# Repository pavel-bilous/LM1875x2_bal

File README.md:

# Two paralleled LM1875 ICs schematics and PCB design

Benefits of using two chips in parallel include: increase of the output drive capability of an amplifier, reduced voltage noise (better SNR), and reduced output offset error.

Resources used to design this amp:

Official datasheet - [https://www.ti.com/lit/gpn/lm1875](https://www.ti.com/lit/gpn/lm1875)

## PCB rendered in 3d:

## Schematics:

Two paralleled LM1875 are used to double the current drive and to increase the power output. Safe voltage to power the amplifier is 28V.
Gain is set to a minimum recommended in the datasheet of 10 V/V.

## PCB layout:

Bottom layer is GND. Top layer is signal + power and GND poured in between. Stiching vias are then applied to connect bottom and top GND planes to ensure those are as close to 0 as possible.

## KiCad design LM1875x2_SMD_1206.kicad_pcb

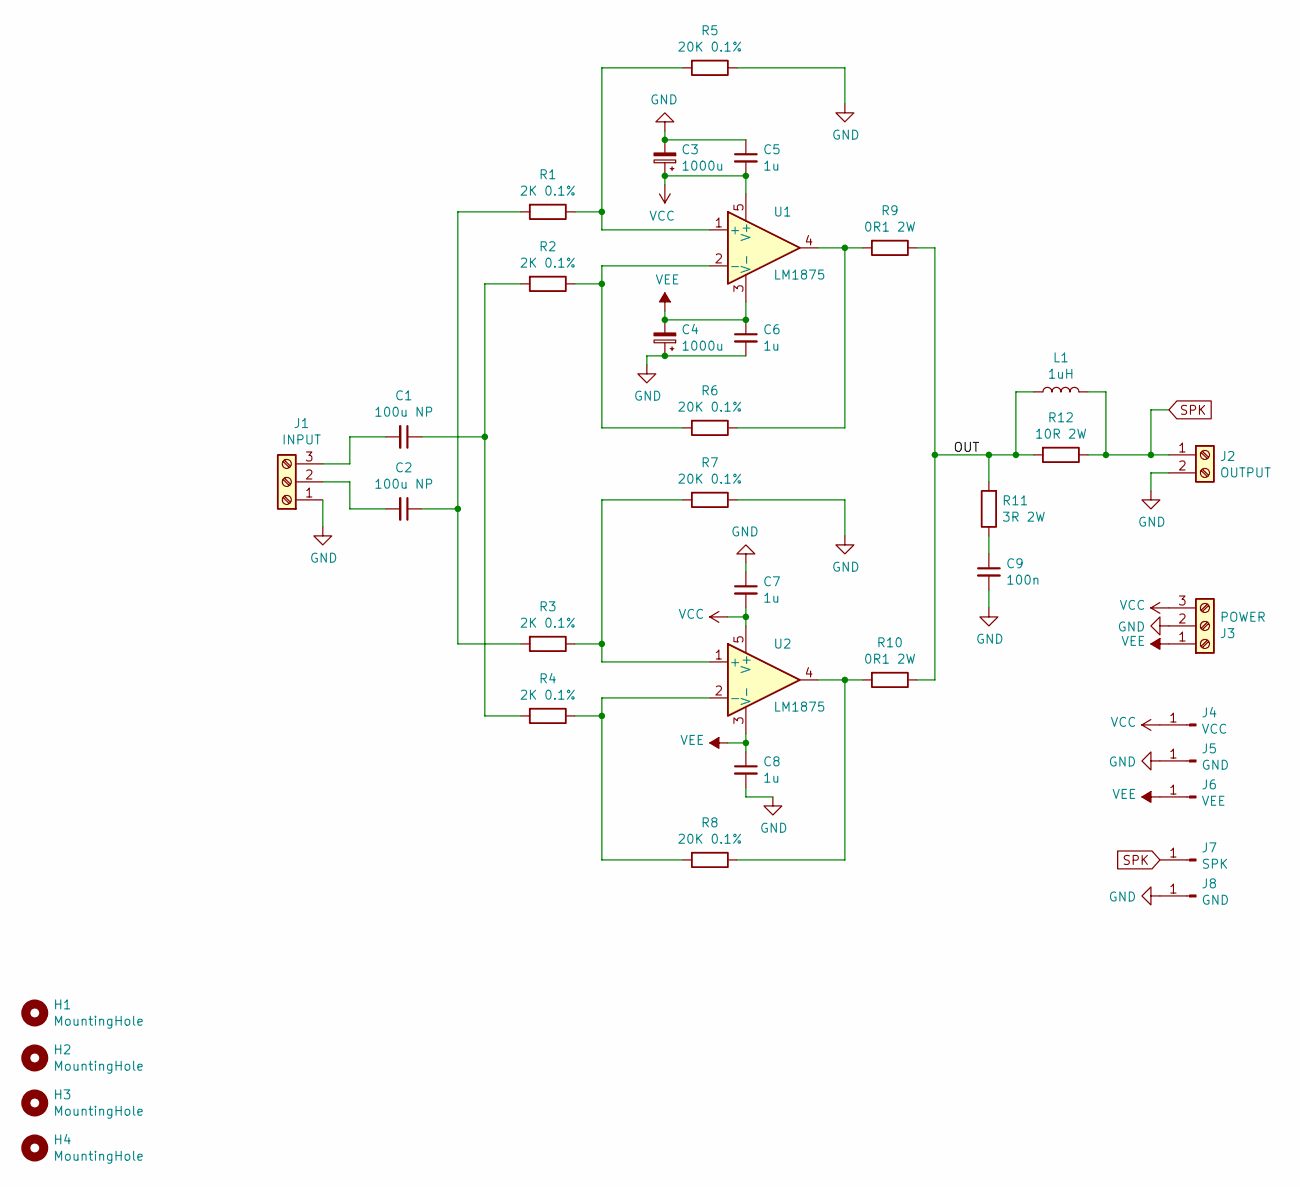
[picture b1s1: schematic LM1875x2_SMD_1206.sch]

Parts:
C1, C2: 100u NP; C_Radial_D10.0mm_H16.0mm_P5.00mm
C3, C4: 1000u; CP_Radial_D16.0mm_P7.50mm
C5, C6, C7, C8: 1u; C_1206_3216Metric_Pad1.42x1.75mm_HandSolder
C9: 100n; C_Rect_L7.2mm_W2.5mm_P5.00mm_FKS2_FKP2_MKS2_MKP2
H1, H2, H3, H4: MountingHole; MountingHole_3.5mm_Pad_Via
J1: INPUT; TerminalBlock_ Amphenol_01_03_P3.50mm
J2: OUTPUT; TerminalBlock_CUI_01x02_P5.00mm
J3: POWER; TerminalBlock_CUI_01x03_P5.00mm
J4: VCC; Terminal_.25_PCB_TAB_TE_Connectivity_P5.08mm_
J5, J8: GND; Terminal_.25_PCB_TAB_TE_Connectivity_P5.08mm_
J6: VEE; Terminal_.25_PCB_TAB_TE_Connectivity_P5.08mm_
J7: SPK; Terminal_.25_PCB_TAB_TE_Connectivity_P5.08mm_
L1: 1uH; Inductor_DIY_flipped
R1, R2, R3, R4: 2K 0.1%; R_1206_3216Metric
R5, R6, R7, R8: 20K 0.1%; R_1206_3216Metric
R9, R10: 0R1 2W; R_Axial_DIN0614_L14.3mm_D5.7mm_P20.32mm_Horizontal
R11: 3R 2W; R_Axial_DIN0614_L14.3mm_D5.7mm_P20.32mm_Horizontal
R12: 10R 2W; R_Axial_DIN0614_L14.3mm_D5.7mm_P20.32mm_Horizontal
U1, U2: LM1875; TO-220-5_P3.4x3.7mm_StaggerOdd_Lead3.8mm_Vertical

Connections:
/OUT: L1.1, R9.1, R10.1, R11.2, R12.2
GND: C3.2, C4.1, C5.1, C6.2, C7.1, C8.2, C9.2, J1.1, J2.2, J3.2, J5.1, J8.1, R5.1, R7.1
unnamed: C1.1, R2.2, R4.2
unnamed: C1.2, J1.3
unnamed: C2.1, R1.2, R3.2
unnamed: C2.2, J1.2
unnamed: C9.1, R11.1
unnamed: R1.1, R5.2, U1.1 (+)
unnamed: R2.1, R6.2, U1.2 (-)
unnamed: R3.1, R7.2, U2.1 (+)
unnamed: R4.1, R8.2, U2.2 (-)
unnamed: R6.1, R9.2, U1.4
unnamed: R8.1, R10.2, U2.4
SPK: J2.1, J7.1, L1.2, R12.1
VCC: C3.1, C5.2, C7.2, J3.3, J4.1, U1.5 (V+), U2.5 (V+)
VEE: C4.2, C6.1, C8.1, J3.1, J6.1, U1.3 (V-), U2.3 (V-)

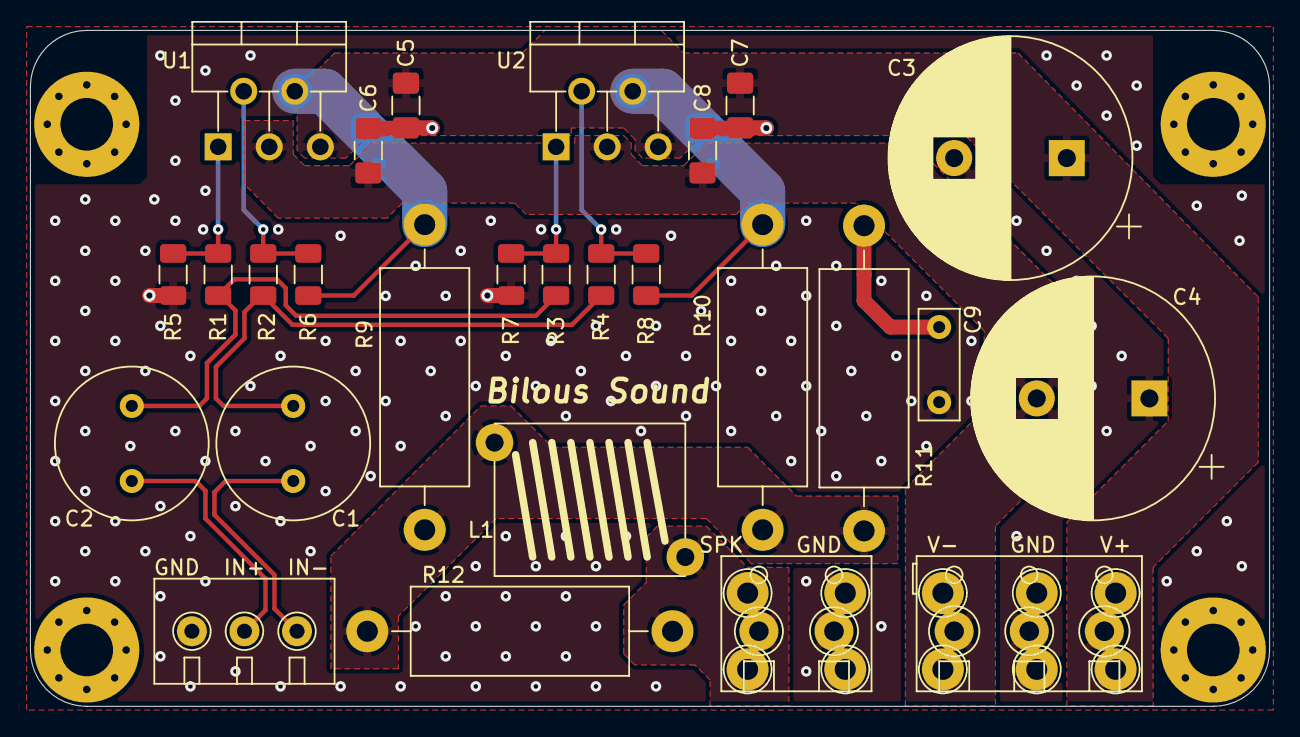
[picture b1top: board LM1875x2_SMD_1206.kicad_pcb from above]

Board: 2 copper layers, 82.5 x 45.0 mm, 36 parts (0 on the bottom side), 16 nets.

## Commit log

2023-04-15 Create temp
2023-05-04 rearranged elements
2023-05-05 finished layout
2023-05-05 added images
2023-05-05 added production files
2023-05-06 updated film cap footprint
2023-05-06 updates images
2023-05-07 minor fixes
